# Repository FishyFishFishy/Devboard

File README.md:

# Devboard
This is a simple devboard that uses an RP2040

I recently developed an interest in electrical engineering a couple months ago, but was not sure where to start. I've followed the hackclub blueprint instructions to help me build this devboard. The purpose of building this was to get practice with pcb design on KiCad. I also hope to be able to use this devboard for a future project with making an inverted pendulum.

You can use this devboard by plugging it in via USB Type-C and flashing whatever you need onto it.

3D Model:

PCB Routing:

Schematic:

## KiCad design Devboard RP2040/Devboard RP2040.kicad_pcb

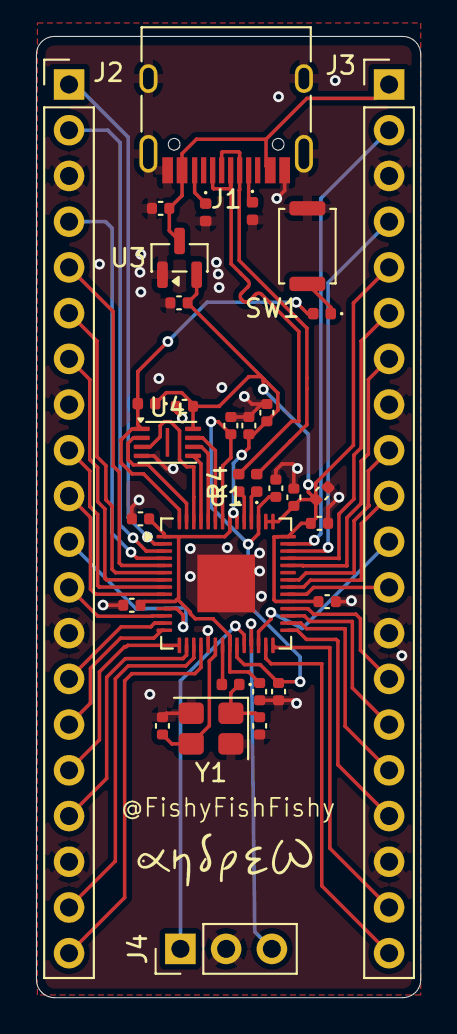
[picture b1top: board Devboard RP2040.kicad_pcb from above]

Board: 2 copper layers, 21.4 x 53.4 mm, 33 parts (0 on the bottom side), 52 nets.

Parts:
C1, C10: +1uF; C_0402_1005Metric
C2, C3, C4, C5, C6, C7, C8, C9, C11, C12: +0.1uF; C_0402_1005Metric
C13, C14: 10uF; C_0402_1005Metric
C15, C16: 33pF; C_0402_1005Metric
C17: 0.1uF; C_0402_1005Metric
J1: USB_C_Receptacle_USB2.0_14P; USB_C_Receptacle_HRO_TYPE-C-31-M-12
J2, J3: Conn_01x20; PinHeader_1x20_P2.54mm_Vertical
J4: Conn_01x03; PinHeader_1x03_P2.54mm_Vertical
R1, R2: 5.1k; D_0402_1005Metric
R3, R4: 27; D_0402_1005Metric
R5, R6: 1k; D_0402_1005Metric
R7: 10k; D_0402_1005Metric
SW1: SW_Push; SW_Push_SPST_NO_Alps_SKRK
U1: RP2040; QFN-56-1EP_7x7mm_P0.4mm_EP3.2x3.2mm
U3: MCP1700x-330xxTT; SOT-23
U4: W25Q16JVSS; Winbond_USON-8-1EP_3x2mm_P0.5mm_EP0.2x1.6mm
Y1: 12 MHz; Crystal_SMD_3225-4Pin_3.2x2.5mm

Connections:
+1V1: C10.1, C11.1, C12.1, U1.23 (DVDD), U1.45 (VREG_VOUT), U1.50 (DVDD)
+3V3: C1.1, C2.1, C3.1, C4.1, C5.1, C6.1, C7.1, C8.1, C9.1, C14.1, C17.1, J3.5, R7.1, U1.1 (IOVDD), U1.10 (IOVDD), U1.22 (IOVDD), U1.33 (IOVDD), U1.42 (IOVDD), U1.43 (ADC_AVDD), U1.44 (VREG_VIN), U1.48 (USB_VDD), U1.49 (IOVDD), U3.2 (VO), U4.8 (VCC)
GND: C1.2, C2.2, C3.2, C4.2, C5.2, C6.2, C7.2, C8.2, C9.2, C10.2, C11.2, C12.2, C13.2, C14.2, C15.1, C16.1, C17.2, J1.A1 (GND), J1.A12 (GND), J1.B1 (GND), J1.B12 (GND), J1.S1 (SHIELD), J2.3, J2.8, J2.13, J2.18, J3.3, J3.8, J3.13, J3.18, J4.2, R1.2, R2.2, SW1.1, U1.19 (TESTEN), U1.57 (GND), U3.1 (GND), U4.4 (GND), Y1.2 (G), Y1.4 (G)
GPIO0: J2.1, U1.2 (GPIO0)
GPIO1: J2.2, U1.3 (GPIO1)
GPIO2: J2.4, U1.4 (GPIO2)
GPIO3: J2.5, U1.5 (GPIO3)
GPIO4: J2.6, U1.6 (GPIO4)
GPIO5: J2.7, U1.7 (GPIO5)
GPIO6: J2.9, U1.8 (GPIO6)
GPIO7: J2.10, U1.9 (GPIO7)
GPIO8: J2.11, U1.11 (GPIO8)
GPIO9: J2.12, U1.12 (GPIO9)
GPIO10: J2.14, U1.13 (GPIO10)
GPIO11: J2.15, U1.14 (GPIO11)
GPIO12: J2.16, U1.15 (GPIO12)
GPIO13: J2.17, U1.16 (GPIO13)
GPIO14: J2.19, U1.17 (GPIO14)
GPIO15: J2.20, U1.18 (GPIO15)
GPIO16: J3.20, U1.27 (GPIO16)
GPIO17: J3.19, U1.28 (GPIO17)
GPIO18: J3.17, U1.29 (GPIO18)
GPIO19: J3.16, U1.30 (GPIO19)
GPIO20: J3.15, U1.31 (GPIO20)
GPIO21: J3.14, U1.32 (GPIO21)
GPIO22: J3.12, U1.34 (GPIO22)
GPIO23: J3.10, U1.35 (GPIO23)
GPIO24: J3.9, U1.36 (GPIO24)
GPIO26/ADC0: J3.7, U1.38 (GPIO26/ADC0)
GPIO27/ADC1: J3.6, U1.39 (GPIO27/ADC1)
GPIO28/ADC2: J3.4, U1.40 (GPIO28/ADC2)
GPIO29/ADC3: J3.2, U1.41 (GPIO29/ADC3)
unnamed: C16.2, R5.1, Y1.1
unnamed: J1.A5 (CC1), R1.1
unnamed: J1.B5 (CC2), R2.1
unnamed: R6.1, SW1.2
unnamed: R3.1, U1.46 (USB_DM)
unnamed: R4.1, U1.47 (USB_DP)
QSPI_SCLK: U1.52 (QSPI_SCLK), U4.6 (CLK)
QSPI_SD0: U1.53 (QSPI_SD0), U4.5 (DI/IO_{0})
QSPI_SD1: U1.55 (QSPI_SD1), U4.2 (DO/IO_{1})
QSPI_SD2: U1.54 (QSPI_SD2), U4.3 (~WP/IO_{2})
QSPI_SD3: U1.51 (QSPI_SD3), U4.7 (~HOLD/~RESET/IO_{3})
QSPI_SS: R6.2, R7.2, U1.56 (~QSPI_SS), U4.1 (~CS)
RUN: J3.11, U1.26 (RUN)
SWCLK: J4.1, U1.24 (SWCLK)
SWDIO: J4.3, U1.25 (SWDIO)
USBD+: J1.A6 (D+), J1.B6 (D+), R4.2
USBD-: J1.A7 (D-), J1.B7 (D-), R3.2
VBUS: C13.1, J1.A4 (VBUS), J1.A9 (VBUS), J1.B4 (VBUS), J1.B9 (VBUS), J3.1, U3.3 (VI)
XIN: C15.2, U1.20 (XIN), Y1.3
XOUT: R5.2, U1.21 (XOUT)

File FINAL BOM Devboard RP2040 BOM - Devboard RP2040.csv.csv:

Id,Designator,Footprint,Quantity,Comment,Supplier and ref
1,"R4,R3",D_0402_1005Metric,2,27,
2,"R2,R1",D_0402_1005Metric,2,5.1k,
3,"J2,J3",PinHeader_1x20_P2.54mm_Vertical,2,Conn_01x20,
4,"C15,C16",C_0402_1005Metric,2,33pF,
5,"C5,C11,C9,C7,C8,C2,C4,C12,C3,C6",C_0402_1005Metric,10,+0.1uF,
6,Y1,Crystal_SMD_3225-4Pin_3.2x2.5mm,1,12 MHz,
7,J1,USB_C_Receptacle_HRO_TYPE-C-31-M-12,1,USB_C_Receptacle_USB2.0_14P,
8,"C1,C10",C_0402_1005Metric,2,+1uF,
9,"R6,R5",D_0402_1005Metric,2,1k,
10,R7,D_0402_1005Metric,1,10k,
11,SW1,SW_Push_SPST_NO_Alps_SKRK,1,SW_Push,
12,U1,QFN-56-1EP_7x7mm_P0.4mm_EP3.2x3.2mm,1,RP2040,
13,C17,C_0402_1005Metric,1,0.1uF,
14,J4,PinHeader_1x03_P2.54mm_Vertical,1,Conn_01x03,
15,U3,SOT-23,1,MCP1700x-330xxTT,
16,U4,Winbond_USON-8-1EP_3x2mm_P0.5mm_EP0.2x1.6mm,1,W25Q16JVSS,
17,"C14,C13",C_0402_1005Metric,2,10uF,

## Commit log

2026-02-16 Update README with project details and usage instructions
    Expanded the description of the devboard project, detailing its purpose and usage.
2026-02-16 Fix typo in README.md regarding RP2040
2026-02-26 Add image to README for devboard illustration
    Added an image to illustrate the devboard usage.
2026-02-26 Update README.md with PCB images
    Added images for 3D PCB, PCB Routing, and Schematic.
2026-02-26 Updated BOM
2026-02-26 Devbaord RP2040.step file
2026-02-26 Basic LED blinking firmware for testing
2026-03-09 Update README formatting for clarity
